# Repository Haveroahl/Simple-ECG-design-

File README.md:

# Simple ECG design
#This is a group project focused on designing a simple ECG signal acquisition circuit. The initial design used the u741 operational amplifier, and later improvements were made using the TL072 for enhanced performance.

# Flow 
• Researched and analyzed the components of a basic ECG circuit, including an instrumentation amplifier, a 4th-order low-pass Sallen-Key filter, and a twin-T notch filter using the u741 OpAmp.<br>
• Calculated appropriate component values for circuit design, simulated ECG waveforms with added noise using LTspice, and tested the circuit on a breadboard.<br>
• Designed schematic and PCB layout, and assembled the circuit on a PCB.

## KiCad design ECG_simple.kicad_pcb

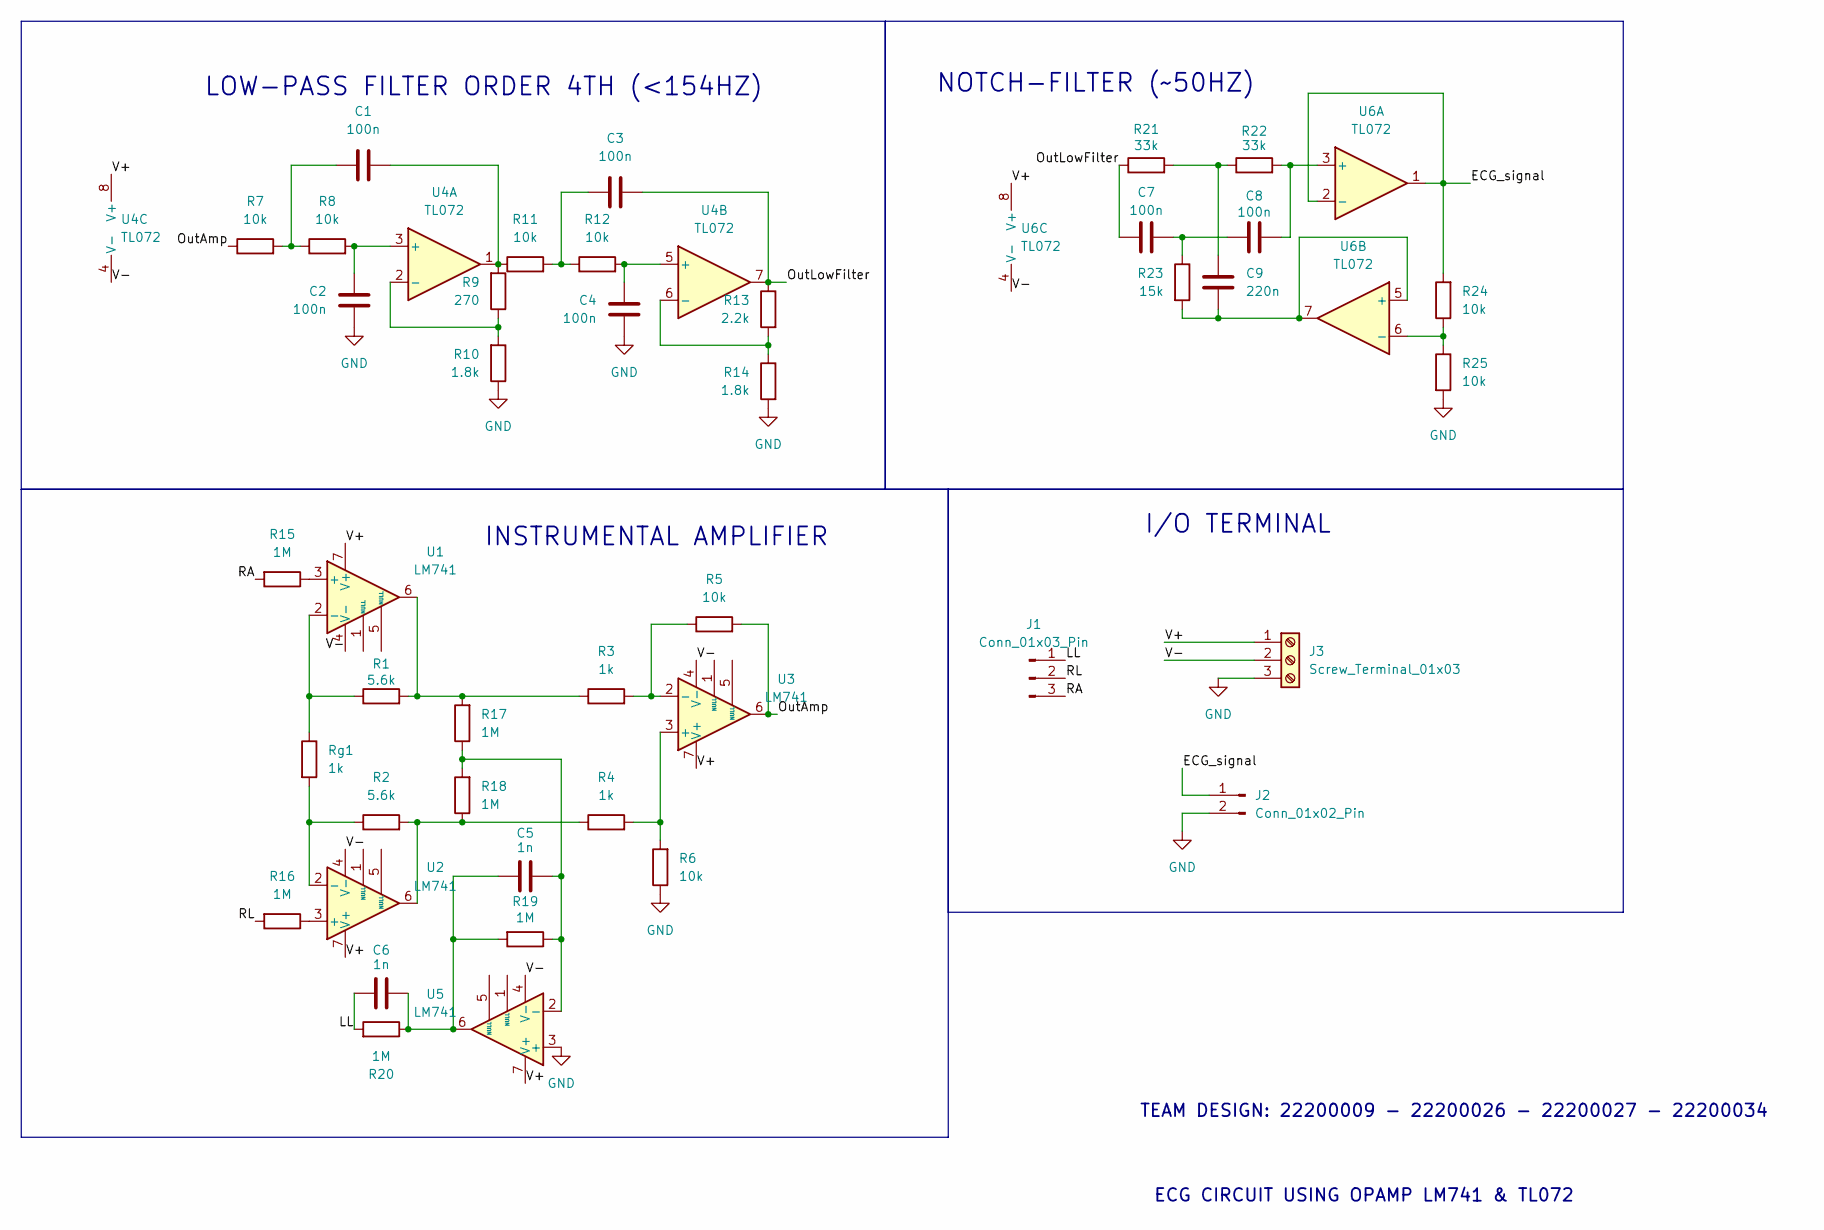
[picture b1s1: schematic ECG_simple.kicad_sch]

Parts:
C1, C2, C3, C4, C7, C8: 100n; C_Rect_L9.0mm_W3.2mm_P7.50mm_MKT
C5, C6: 1n; C_Rect_L9.0mm_W3.2mm_P7.50mm_MKT
C9: 220n; C_Rect_L9.0mm_W3.2mm_P7.50mm_MKT
J1: Conn_01x03_Pin; PinSocket_1x03_P2.54mm_Vertical
J2: Conn_01x02_Pin; PinHeader_1x02_P2.54mm_Vertical
J3: Screw_Terminal_01x03; TerminalBlock_Altech_AK300-3_P5.00mm
R1, R2: 5.6k; R_Axial_DIN0207_L6.3mm_D2.5mm_P10.16mm_Horizontal
R3, R4: 1k; R_Axial_DIN0207_L6.3mm_D2.5mm_P10.16mm_Horizontal
R5, R6, R7, R8, R11, R12, R24, R25: 10k; R_Axial_DIN0207_L6.3mm_D2.5mm_P10.16mm_Horizontal
R9: 270; R_Axial_DIN0207_L6.3mm_D2.5mm_P10.16mm_Horizontal
R10, R14: 1.8k; R_Axial_DIN0207_L6.3mm_D2.5mm_P10.16mm_Horizontal
R13: 2.2k; R_Axial_DIN0207_L6.3mm_D2.5mm_P10.16mm_Horizontal
R15, R16, R17, R18, R19, R20: 1M; R_Axial_DIN0207_L6.3mm_D2.5mm_P10.16mm_Horizontal
R21, R22: 33k; R_Axial_DIN0207_L6.3mm_D2.5mm_P10.16mm_Horizontal
R23: 15k; R_Axial_DIN0207_L6.3mm_D2.5mm_P10.16mm_Horizontal
Rg1: 1k; R_Axial_DIN0207_L6.3mm_D2.5mm_P10.16mm_Horizontal
U1, U2, U3, U5: LM741; DIP-8_W7.62mm_Socket_LongPads
U4, U6: TL072; DIP-8_W7.62mm_Socket_LongPads

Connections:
/ECG_signal: J2.1, R24.2, U6.1, U6.2 (-)
/LL: C6.1, J1.1, R20.2
/OutAmp: R5.2, R7.1, U3.6
/OutLowFilter: C3.2, C7.2, R13.1, R21.1, U4.7
/RA: J1.3, R15.2
/RL: J1.2, R16.2
/V+: J3.1, U1.7 (V+), U2.7 (V+), U3.7 (V+), U4.8 (V+), U5.7 (V+), U6.8 (V+)
/V-: J3.2, U1.4 (V-), U2.4 (V-), U3.4 (V-), U4.4 (V-), U5.4 (V-), U6.4 (V-)
GND: C2.2, C4.2, J2.2, J3.3, R6.1, R10.1, R14.2, R25.2, U5.3 (+)
unnamed: C1.1, R7.2, R8.1
unnamed: C1.2, R9.2, R11.1, U4.1
unnamed: C3.1, R11.2, R12.1
unnamed: C5.1, C6.2, R19.2, R20.1, U5.6
unnamed: C7.1, C8.2, R23.1
unnamed: C9.1, R21.2, R22.1
unnamed: R1.2, R3.1, R17.2, U1.6
unnamed: R2.2, R4.1, R18.1, U2.6
unnamed: R15.1, U1.3 (+)
unnamed: R1.1, Rg1.1, U1.2 (-)
unnamed: R16.1, U2.3 (+)
unnamed: R2.1, Rg1.2, U2.2 (-)
unnamed: R4.2, R6.2, U3.3 (+)
unnamed: R3.2, R5.1, U3.2 (-)
unnamed: C2.1, R8.2, U4.3 (+)
unnamed: R9.1, R10.2, U4.2 (-)
unnamed: C4.1, R12.2, U4.5 (+)
unnamed: R13.2, R14.1, U4.6 (-)
unnamed: C5.2, R17.1, R18.2, R19.1, U5.2 (-)
unnamed: C8.1, R22.2, U6.3 (+)
unnamed: C9.2, R23.2, U6.5 (+), U6.7
unnamed: R24.1, R25.1, U6.6 (-)

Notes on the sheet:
INSTRUMENTAL AMPLIFIER
LOW-PASS FILTER ORDER 4TH (<154HZ)
ECG CIRCUIT USING OPAMP LM741 & TL072
I/O TERMINAL
TEAM DESIGN: 22200009 - 22200026 - 22200027 - 22200034
NOTCH-FILTER (~50HZ)

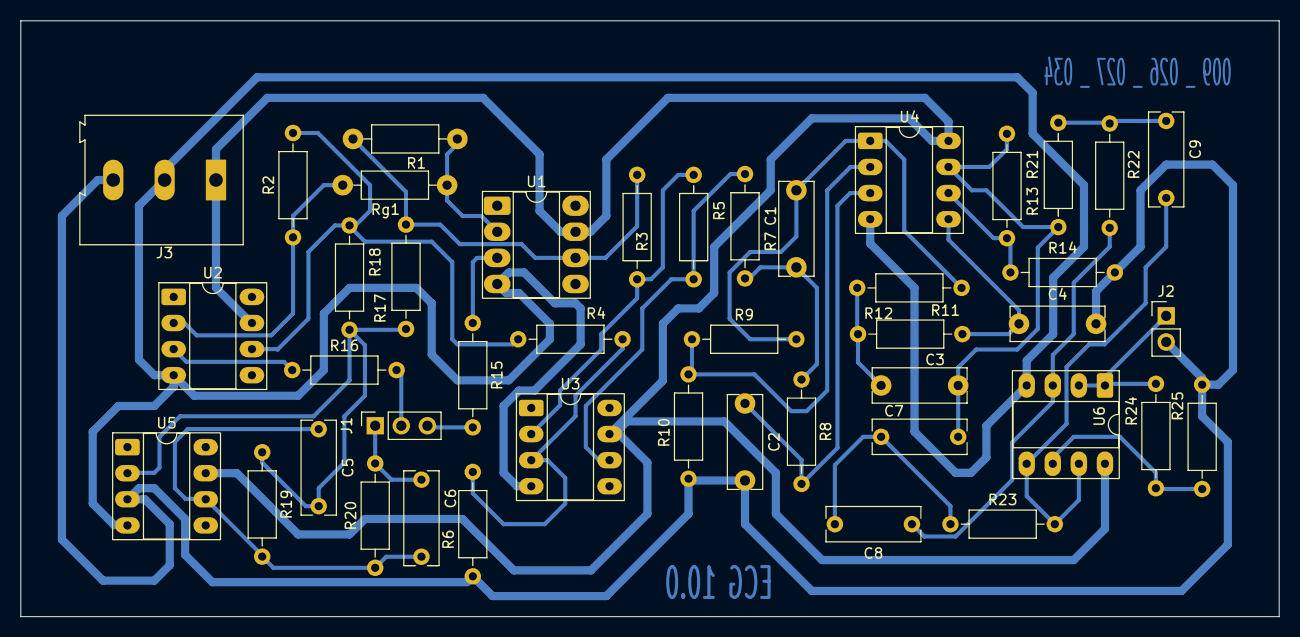
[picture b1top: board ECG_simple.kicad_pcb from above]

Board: 2 copper layers, 122.5 x 58.0 mm, 44 parts (0 on the bottom side), 31 nets.
